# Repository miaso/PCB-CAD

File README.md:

# PCB-CAD
Archive for some of PCBs

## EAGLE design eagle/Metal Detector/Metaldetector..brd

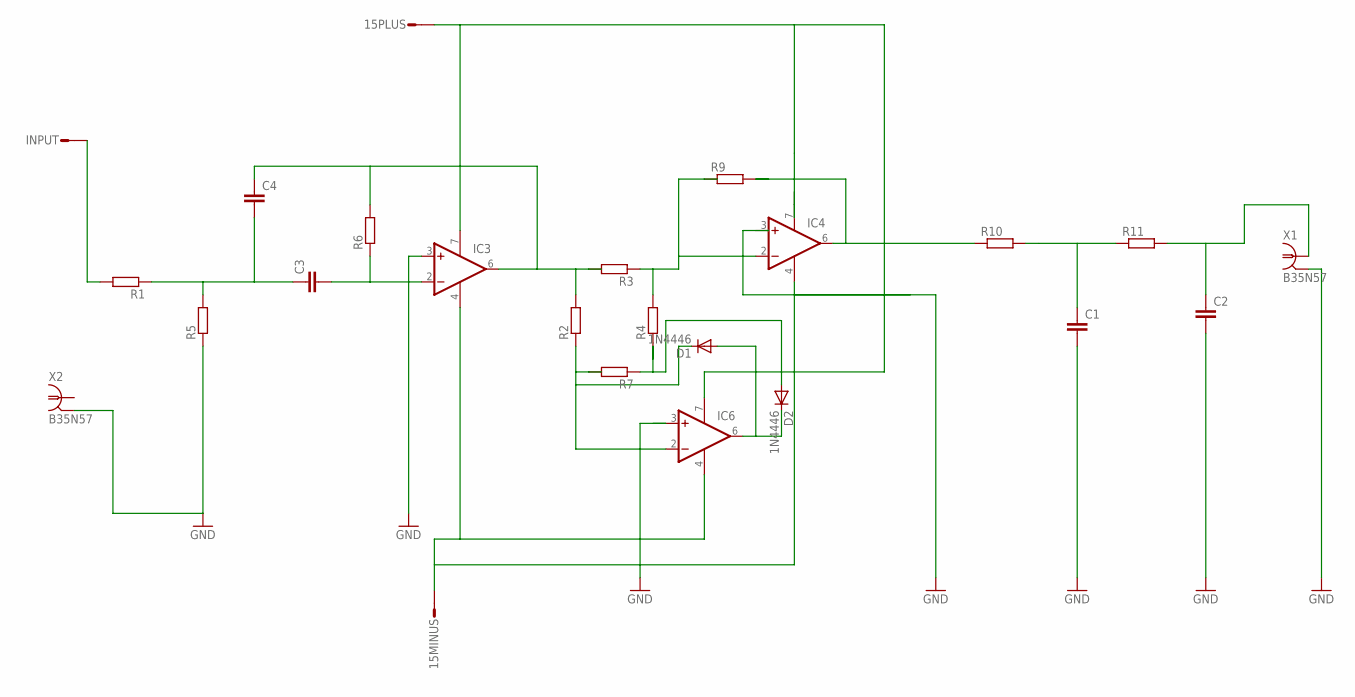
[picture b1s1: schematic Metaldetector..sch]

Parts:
15MINUS, 15PLUS: ST2,8
C1, C2: C-EU025-040X050; C025-040X050
C3, C4: C2.5/5; C2.5-5
D1, D2: 1N4446; DO35-10
IC3, IC4, IC6: 1AMP_P7+4N; DIL08
INPUT: ST2,8
R1, R2, R3, R4, R5, R6, R7, R9: R0207/10; 0207/10
R10, R11: R0204/7; 0204/7
X1, X2: B35N57

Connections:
GND: C1.2, C2.2, IC3.3 (+IN), IC4.3 (+IN), IC6.3 (+IN), R5.1, X1.2, X1.3 (2), X1.4 (2), X1.5 (2), X2.2, X2.3 (2), X2.4 (2), X2.5 (2)
unnamed: C1.1, R10.2, R11.1
unnamed: C3.1, C4.2, R1.1, R5.2
unnamed: C3.2, IC3.2 (-IN), R6.1
unnamed: C4.1, IC3.6 (OUT), R2.2, R3.2, R6.2
unnamed: D1.C, IC6.2 (-IN), R2.1, R7.2
unnamed: C2.1, R11.2, X1.1
unnamed: D2.A, R4.1, R7.1
unnamed: IC4.2 (-IN), R3.1, R4.2, R9.1
unnamed: IC4.6 (OUT), R9.2, R10.1
unnamed: 15MINUS.1, IC3.4 (V-), IC4.4 (V-), IC6.4 (V-)
unnamed: D1.A, D2.C, IC6.6 (OUT)
unnamed: INPUT.1, R1.2
unnamed: 15PLUS.1, IC3.7 (V+), IC4.7 (V+), IC6.7 (V+)

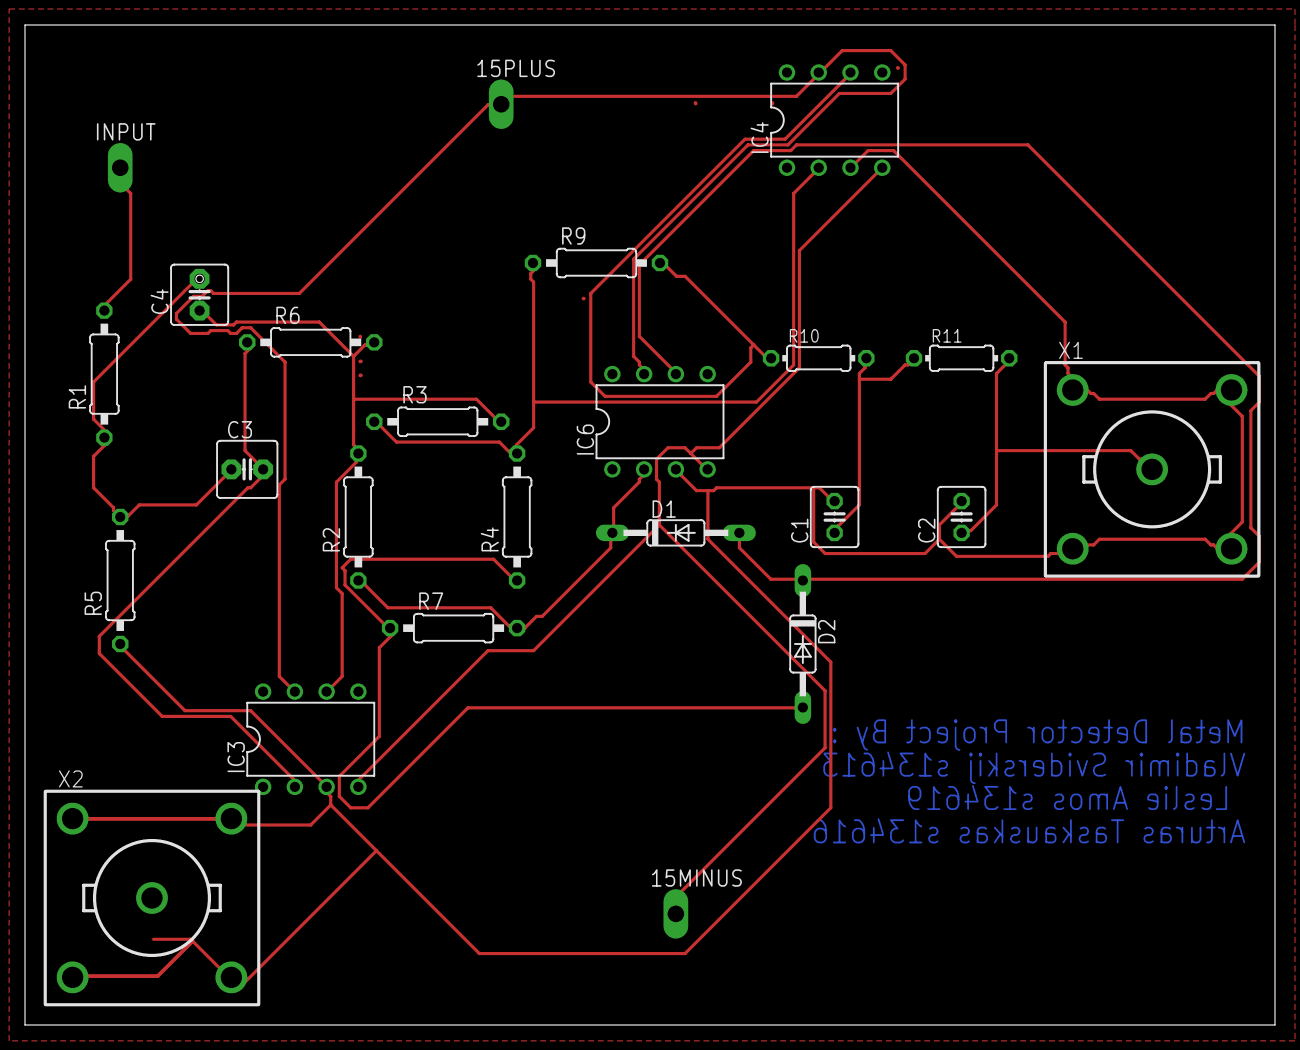
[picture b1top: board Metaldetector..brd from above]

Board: 2 copper layers, 100.0 x 80.0 mm, 24 parts (0 on the bottom side), 14 nets.

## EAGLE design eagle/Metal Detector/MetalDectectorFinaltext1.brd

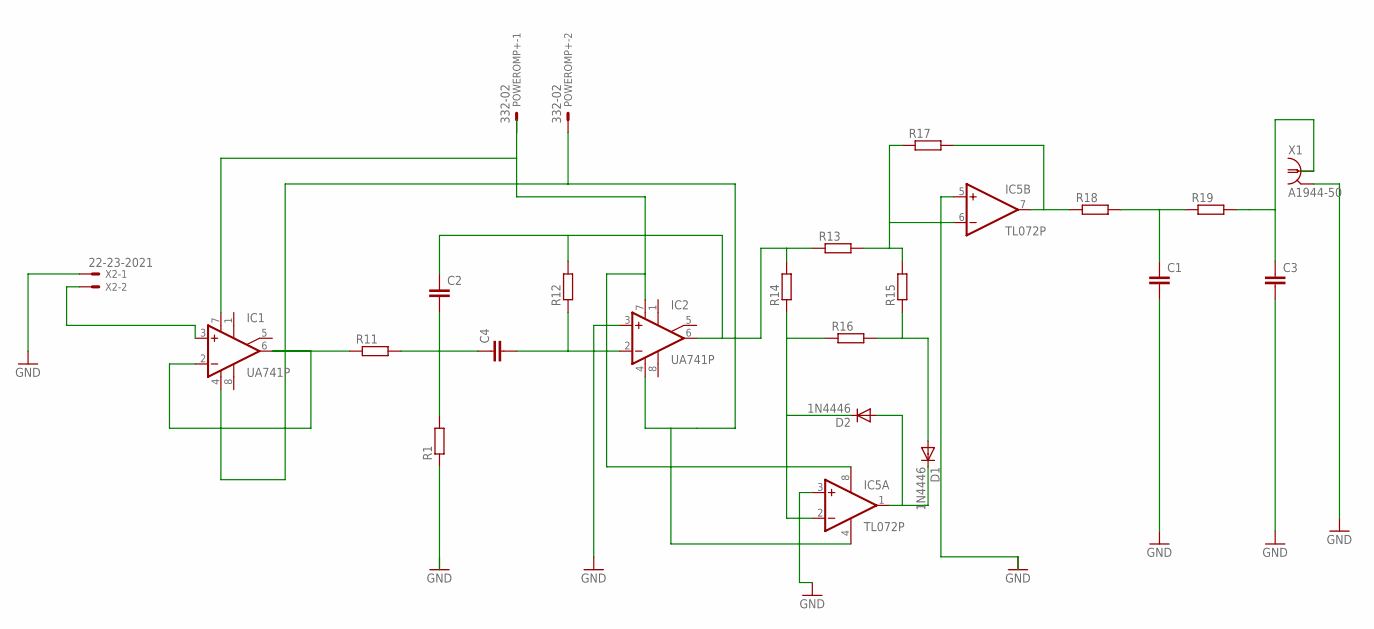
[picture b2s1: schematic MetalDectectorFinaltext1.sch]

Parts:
C1, C2, C3, C4: C-EU025-025X050; C025-025X050
D1, D2: 1N4446; DO35-10
IC1, IC2: UA741P; DIL08
IC5: TL072P; DIL08
POWEROMP+: 332-02
R1, R11, R12, R13, R14, R15, R16, R17, R18, R19: R-EU_0204_7; 0204/7
X1: A1944-50; A1944
X2: 22-23-2021

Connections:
GND: C1.2, C3.2, IC2.3 (+IN), IC5.3 (+IN), IC5.5 (+IN), X1.2, X1.3 (2), X1.4 (2), X1.5 (2), X2.1
unnamed: IC1.3 (+IN), X2.2
unnamed: IC1.2 (-IN), IC1.6 (OUT), R11.1
unnamed: C2.2, C4.1, R1.2, R11.2
unnamed: C2.1, IC2.6 (OUT), R12.2, R13.1, R14.2
unnamed: C4.2, IC2.2 (-IN), R12.1
unnamed: IC1.4 (V-), IC2.4 (V-), IC5.4 (V-), POWEROMP+.2
unnamed: IC5.6 (-IN), R13.2, R15.2, R17.1
unnamed: D2.C, IC5.2 (-IN), R14.1, R16.1
unnamed: D1.C, D2.A, IC5.1 (OUT)
unnamed: IC1.7 (V+), IC2.7 (V+), IC5.8 (V+), POWEROMP+.1
unnamed: IC5.7 (OUT), R17.2, R18.1
unnamed: C1.1, R18.2, R19.1
unnamed: C3.1, R19.2, X1.1
unnamed: D1.A, R15.1, R16.2

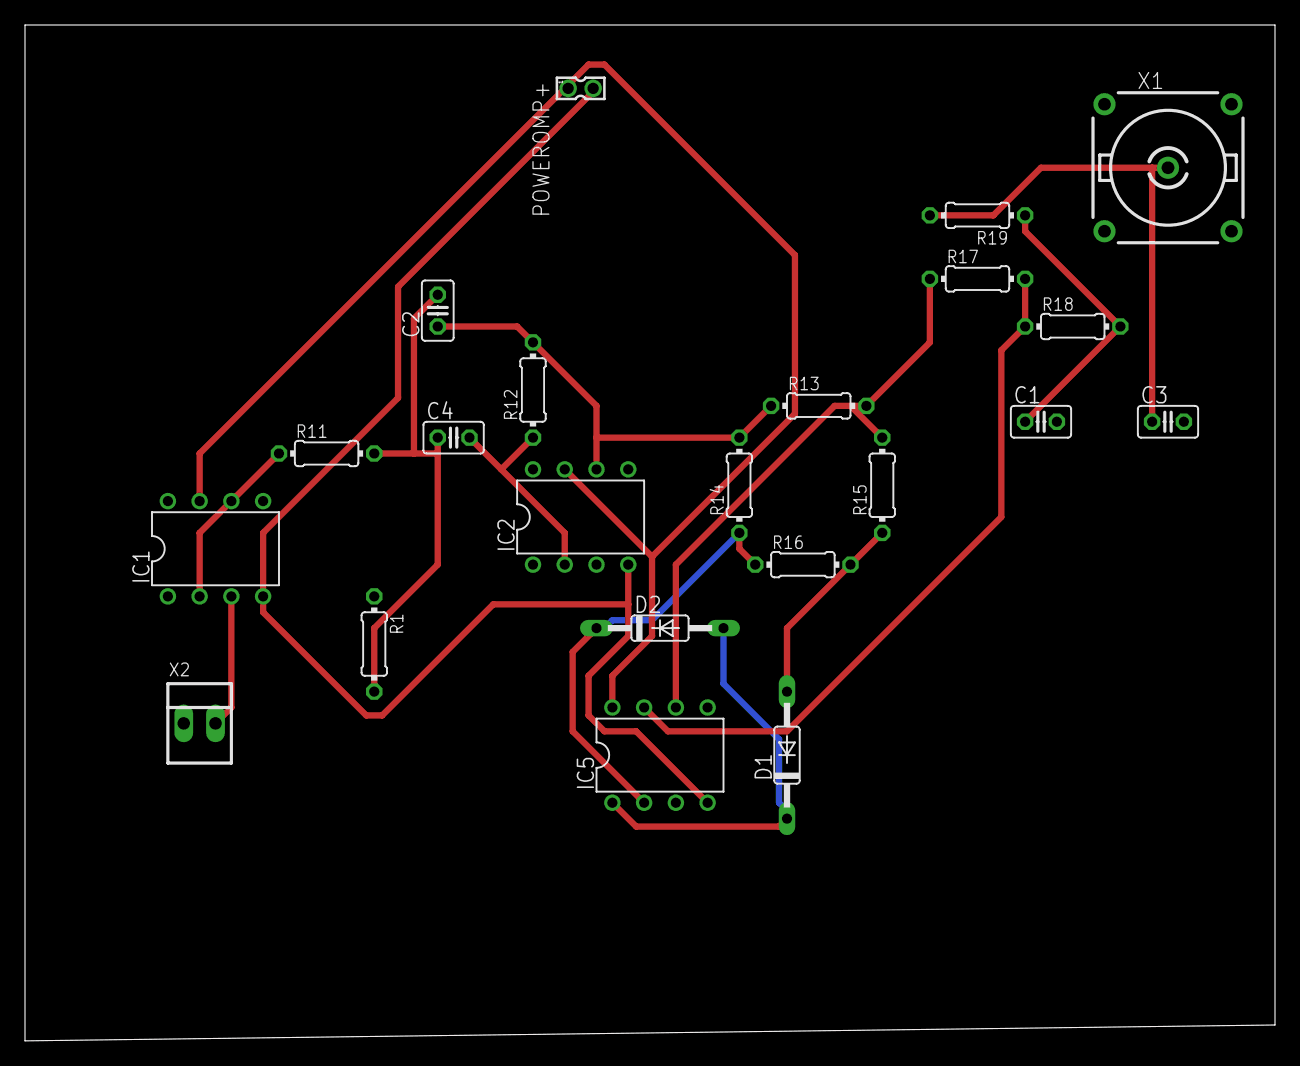
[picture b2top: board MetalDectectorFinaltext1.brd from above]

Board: 2 copper layers, 100.0 x 81.3 mm, 22 parts (0 on the bottom side), 15 nets.

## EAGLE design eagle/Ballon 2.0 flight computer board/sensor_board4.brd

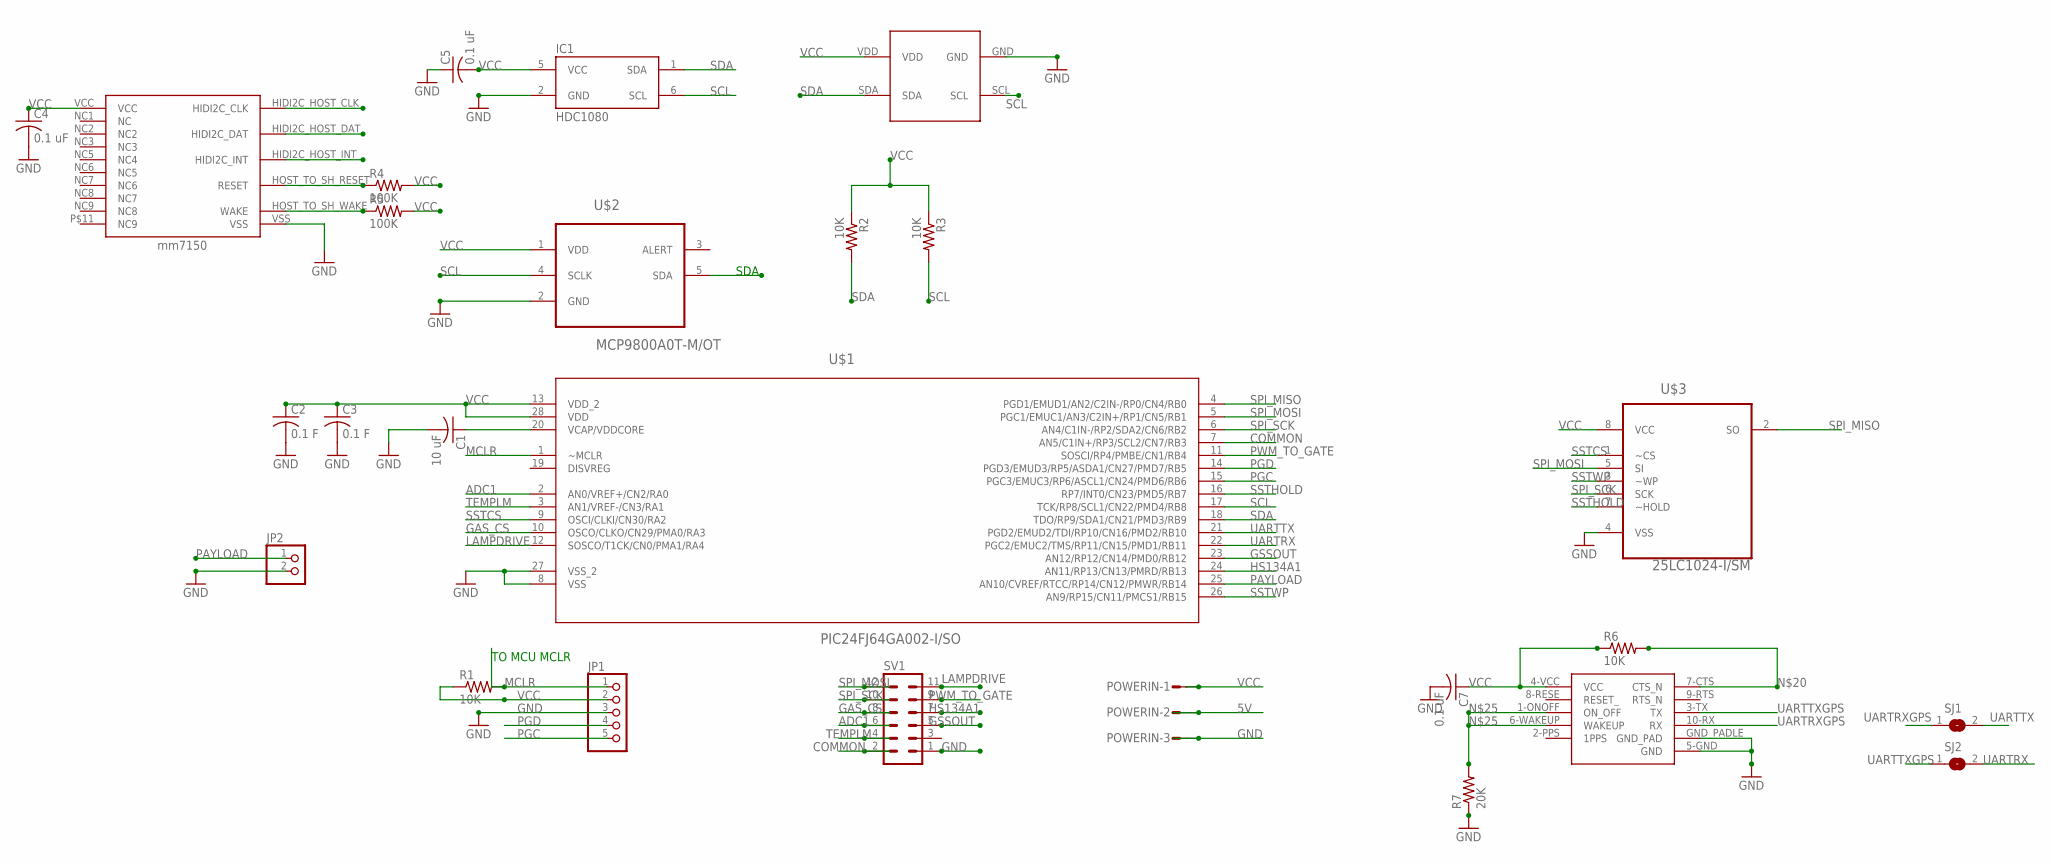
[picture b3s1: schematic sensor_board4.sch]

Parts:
C1: 10 uF; C0805
C2, C3: 0.1 F; C0805
C4, C5, C7: 0.1 uF; C0805
IC1: HDC1080; WSON6
JP1: PINHD-1X5; 1X05
JP2: PINHD-1X2; 1X02
POWERIN: L03P
R1, R2, R3, R6: 10K; M0805
R4, R5: 100K; M0805
R7: 20K; M0805
SJ1, SJ2: SJ
SV1: MA06-2
U$1: PIC24FJ64GA002-I/SO; SOIC127P1030X265-28N
U$2: MCP9800A0T-M/OT; SOT95P280X145-5N
U$3: 25LC1024-I/SM; SOIC127P794X203-8N
U$4: MS5637
U$5: ORG1411; LGA
U$6: MM7150; MM7150-QFN16

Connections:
5V: POWERIN.2
ADC1: SV1.6, U$1.2 (AN0/VREF+/CN2/RA0)
COMMON: SV1.2, U$1.7 (AN5/C1IN+/RP3/SCL2/CN7/RB3)
GAS_CS: SV1.8, U$1.10 (OSCO/CLKO/CN29/PMA0/RA3)
GND: C1.2, C2.2, C3.2, C4.2, C5.1, C7.2, IC1.2 (GND), JP1.3, JP2.2, POWERIN.3, R7.1, SV1.1, U$1.8 (VSS), U$1.27 (VSS_2), U$2.2 (GND), U$3.4 (VSS), U$4.GND, U$5.5-GND (GND), U$5.GND_PADLE (GND_PAD), U$6.VSS
GSSOUT: SV1.5, U$1.23 (AN12/RP12/CN14/PMD0/RB12)
HS134A1: SV1.7, U$1.24 (AN11/RP13/CN13/PMRD/RB13)
LAMPDRIVE: SV1.11, U$1.12 (SOSCO/T1CK/CN0/PMA1/RA4)
MCLR: JP1.1, R1.2, U$1.1 (~MCLR)
unnamed: C1.1, U$1.20 (VCAP/VDDCORE)
unnamed: R4.1, U$6.HOST_TO_SH_RESET (RESET)
unnamed: R5.1, U$6.HOST_TO_SH_WAKE (WAKE)
unnamed: R6.2, U$5.7-CTS (CTS_N)
unnamed: R7.2, U$5.1-ONOFF (ON_OFF), U$5.6-WAKEUP (WAKEUP)
PAYLOAD: JP2.1, U$1.25 (AN10/CVREF/RTCC/RP14/CN12/PMWR/RB14)
PGC: JP1.5, U$1.15 (PGC3/EMUC3/RP6/ASCL1/CN24/PMD6/RB6)
PGD: JP1.4, U$1.14 (PGD3/EMUD3/RP5/ASDA1/CN27/PMD7/RB5)
PWM_TO_GATE: SV1.9, U$1.11 (SOSCI/RP4/PMBE/CN1/RB4)
SCL: IC1.6 (SCL), R3.2, U$1.17 (TCK/RP8/SCL1/CN22/PMD4/RB8), U$2.4 (SCLK), U$4.SCL, U$6.HIDI2C_HOST_CLK (HIDI2C_CLK)
SDA: IC1.1 (SDA), R2.2, U$1.18 (TDO/RP9/SDA1/CN21/PMD3/RB9), U$2.5 (SDA), U$4.SDA, U$6.HIDI2C_HOST_DAT (HIDI2C_DAT)
SPI_MISO: U$1.4 (PGD1/EMUD1/AN2/C2IN-/RP0/CN4/RB0), U$3.2 (SO)
SPI_MOSI: SV1.12, U$1.5 (PGC1/EMUC1/AN3/C2IN+/RP1/CN5/RB1), U$3.5 (SI)
SPI_SCK: SV1.10, U$1.6 (AN4/C1IN-/RP2/SDA2/CN6/RB2), U$3.6 (SCK)
SSTCS: U$1.9 (OSCI/CLKI/CN30/RA2), U$3.1 (~CS)
SSTHOLD: U$1.16 (RP7/INT0/CN23/PMD5/RB7), U$3.7 (~HOLD)
SSTWP: U$1.26 (AN9/RP15/CN11/PMCS1/RB15), U$3.3 (~WP)
TEMPLM: SV1.4, U$1.3 (AN1/VREF-/CN3/RA1)
UARTRX: SJ2.2, U$1.22 (PGC2/EMUC2/TMS/RP11/CN15/PMD1/RB11)
UARTRXGPS: SJ1.1, U$5.10-RX (RX)
UARTTX: SJ1.2, U$1.21 (PGD2/EMUD2/TDI/RP10/CN16/PMD2/RB10)
UARTTXGPS: SJ2.1, U$5.3-TX (TX)
VCC: C2.1, C3.1, C4.1, C5.2, C7.1, IC1.5 (VCC), JP1.2, POWERIN.1, R1.1, R2.1, R3.1, R4.2, R5.2, R6.1, U$1.13 (VDD_2), U$1.28 (VDD), U$2.1 (VDD), U$3.8 (VCC), U$4.VDD, U$5.4-VCC (VCC), U$6.VCC

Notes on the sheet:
TO MCU MCLR
SDA

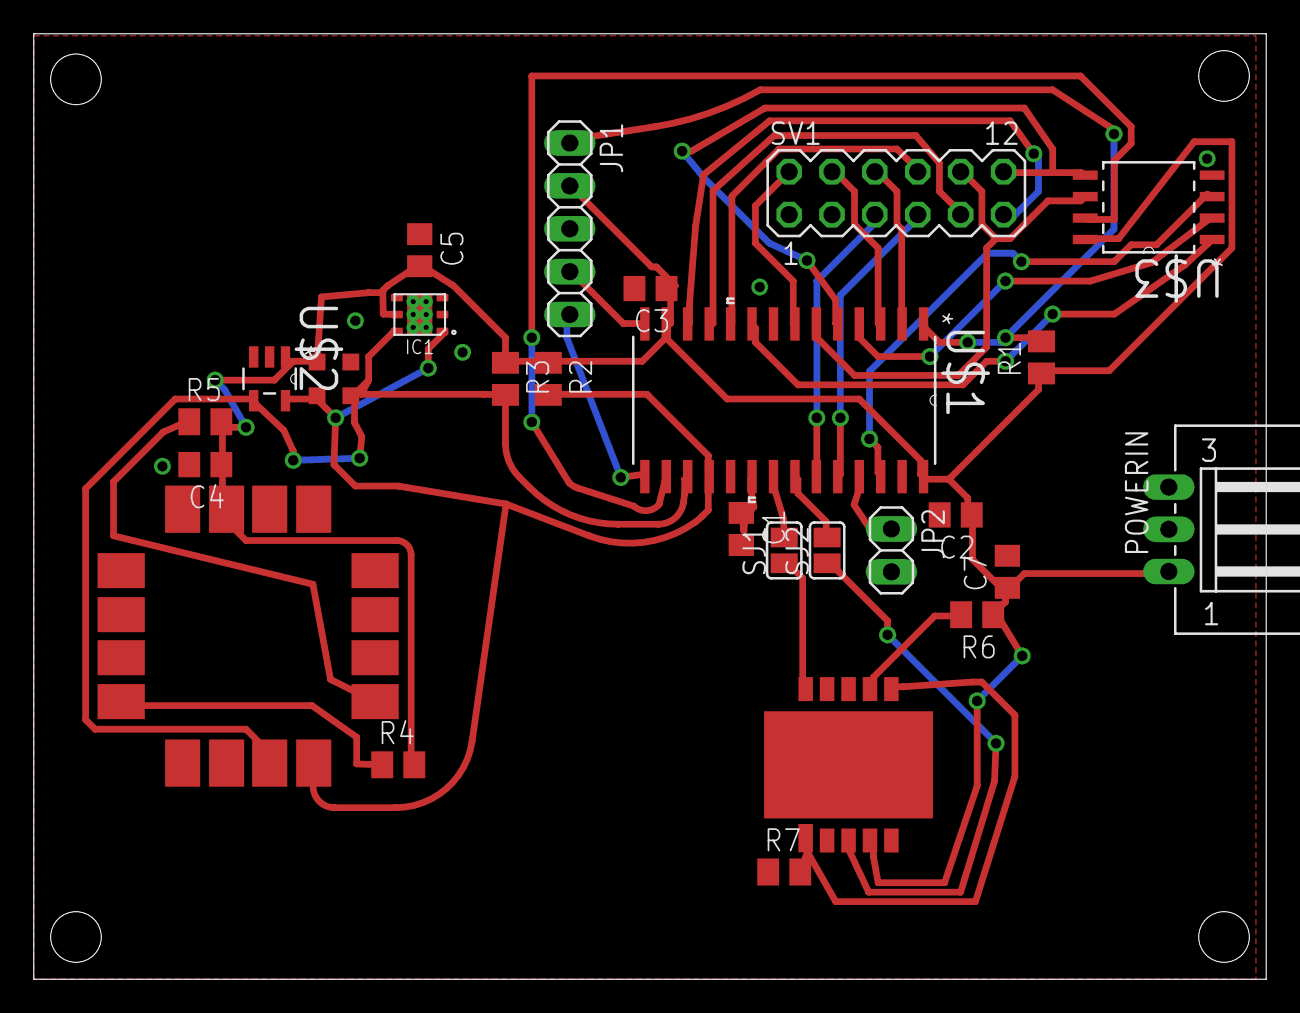
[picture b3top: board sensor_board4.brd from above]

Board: 2 copper layers, 73.0 x 56.0 mm, 26 parts (0 on the bottom side), 31 nets.
